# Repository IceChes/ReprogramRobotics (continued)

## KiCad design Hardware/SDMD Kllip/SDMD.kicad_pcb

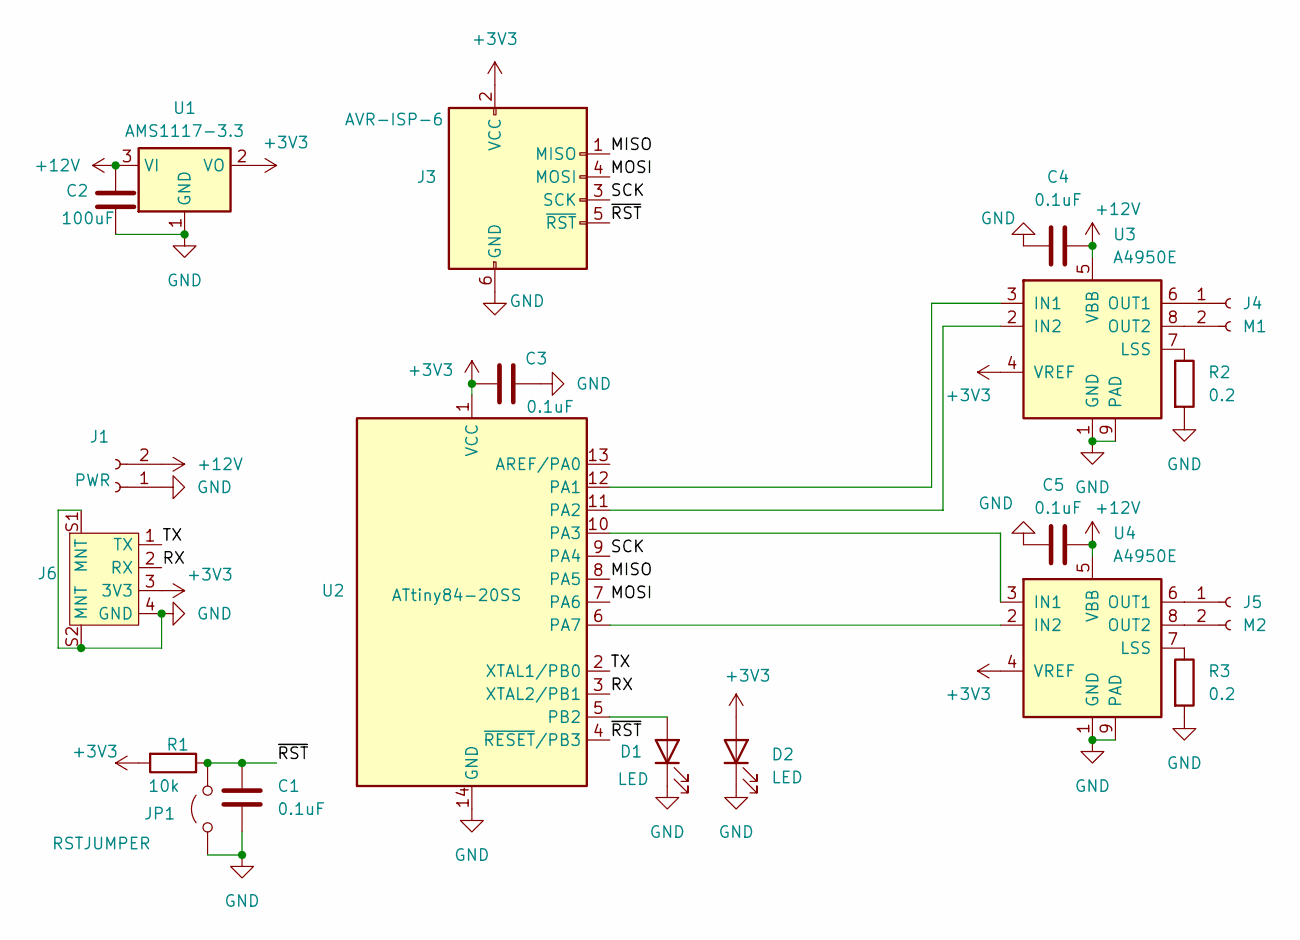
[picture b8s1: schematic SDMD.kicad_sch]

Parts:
C1, C3, C4, C5: 0.1uF; C_0805_2012Metric
C2: 100uF; C_1206_3216Metric
D1, D2: LED; LED_0805_2012Metric
J1: PWR; DoubleWire
J3: AVR-ISP-6; PinHeader_2x03_P2.54mm_Vertical
J4: M1; DoubleWire
J5: M2; DoubleWire
J6: SPARKFUN_PRT-14417
JP1: RSTJUMPER; SolderJumper-2_P1.3mm_Open_Pad1.0x1.5mm
R1: 10k; R_0805_2012Metric
R2, R3: 0.2; R_0805_2012Metric
U1: AMS1117-3.3; SOT-223-3_TabPin2
U2: ATtiny84-20SS; SOIC-14_3.9x8.7mm_P1.27mm
U3, U4: A4950E; SOIC-8-1EP_3.9x4.9mm_P1.27mm_EP2.41x3.3mm

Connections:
+3V3: C3.2, D2.2 (A), J3.2 (VCC), J6.3 (3V3), R1.2, U1.2 (VO), U2.1 (VCC), U3.4 (VREF), U4.4 (VREF)
+12V: C2.2, C4.2, C5.2, J1.2, U1.3 (VI), U3.5 (VBB), U4.5 (VBB)
/MISO: J3.1 (MISO), U2.8 (PA5)
/MOSI: J3.4 (MOSI), U2.7 (PA6)
/RX: J6.2 (RX), U2.3 (XTAL2/PB1)
/SCK: J3.3 (SCK), U2.9 (PA4)
/TX: J6.1 (TX), U2.2 (XTAL1/PB0)
/~RST: C1.2, J3.5 (~RST), JP1.2 (B), R1.1, U2.4 (~RESET/PB3)
GND: C1.1, C2.1, C3.1, C4.1, C5.1, D1.1 (K), D2.1 (K), J1.1, J3.6 (GND), J6.4 (GND), J6.S1 (MNT), J6.S2 (MNT), JP1.1 (A), R2.2, R3.2, U1.1 (GND), U2.14 (GND), U3.1 (GND), U3.9 (PAD), U4.1 (GND), U4.9 (PAD)
unnamed: D1.2 (A), U2.5 (PB2)
unnamed: J4.1, U3.6 (OUT1)
unnamed: J4.2, U3.8 (OUT2)
unnamed: J5.1, U4.6 (OUT1)
unnamed: J5.2, U4.8 (OUT2)
unnamed: U2.12 (PA1), U3.3 (IN1)
unnamed: U2.11 (PA2), U3.2 (IN2)
unnamed: U2.10 (PA3), U4.3 (IN1)
unnamed: U2.6 (PA7), U4.2 (IN2)
unnamed: R2.1, U3.7 (LSS)
unnamed: R3.1, U4.7 (LSS)

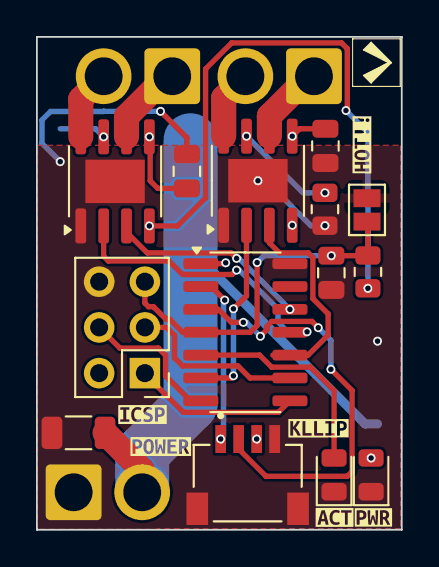
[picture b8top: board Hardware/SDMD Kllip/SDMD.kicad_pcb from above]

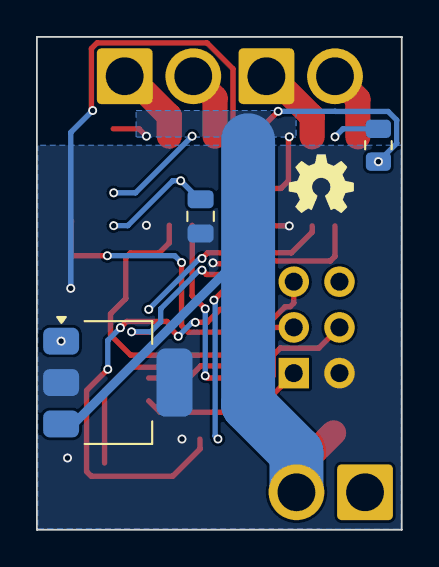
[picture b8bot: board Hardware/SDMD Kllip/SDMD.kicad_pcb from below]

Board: 2 copper layers, 20.3 x 27.4 mm, 28 parts (4 on the bottom side), 20 nets.

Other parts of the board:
kibuzzard-6785EDDE: G***; kibuzzard-6785EDDE
kibuzzard-6785EDEB: G***; kibuzzard-6785EDEB
kibuzzard-6785EE5D: G***; kibuzzard-6785EE5D
kibuzzard-6785EE6F: G***; kibuzzard-6785EE6F
kibuzzard-6785EE54: G***; kibuzzard-6785EE54
kibuzzard-6785EE66: G***; kibuzzard-6785EE66
kibuzzard-6785EE77, kibuzzard-6785EE77#2: G***; kibuzzard-6785EE77

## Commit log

2023-07-29 Full upload
2023-07-29 Big update
2023-08-20 Added Reflection
2023-08-20 Added Reflection (again, it didn't work last time)
2023-08-21 Deleted my beta receiver that I accidentally uploaded.
2023-09-03 HUGE update
2023-09-10 Changed licensing
2023-09-28 Added hardware.
2023-11-11 Large update
2024-03-02 Update basically everything.
2025-01-19 Rework
2025-01-19 oops
2025-01-19 forgot how to markdown
2025-01-21 Assembly guide
2025-01-21 I keep forgetting things
2025-01-23 add gen3 transmitter files
2025-01-26 why do I do this hobby
2025-01-27 doctor's note
2025-02-05 update receiver because the old one doesn't work
2025-02-23 New SDMD firmware based on commands. Docs coming soon.
2025-02-23 new USB receiver based on the Pro Micro
2025-02-26 Redoing the SDMD Kllip in an intelligent way, changing some receiver things, and designing a transmitter board
2025-02-27 I ordered the receiver, tx, and sdmd kllip boards so I hope they work
2025-03-16 Add v3.1
2025-03-25 ear should be a dxf
2025-03-25 I'll clean this up later I promise
2025-03-25 add version number
2025-03-26 organize :3
2025-06-10 Rewrite and push robot firmware to production
2025-06-13 Transmitter 3 firmware
2025-06-24 fix stuff
2025-08-18 Start snapserial project, delete old PCBs.
2025-08-19 WIP of lots of stuff
